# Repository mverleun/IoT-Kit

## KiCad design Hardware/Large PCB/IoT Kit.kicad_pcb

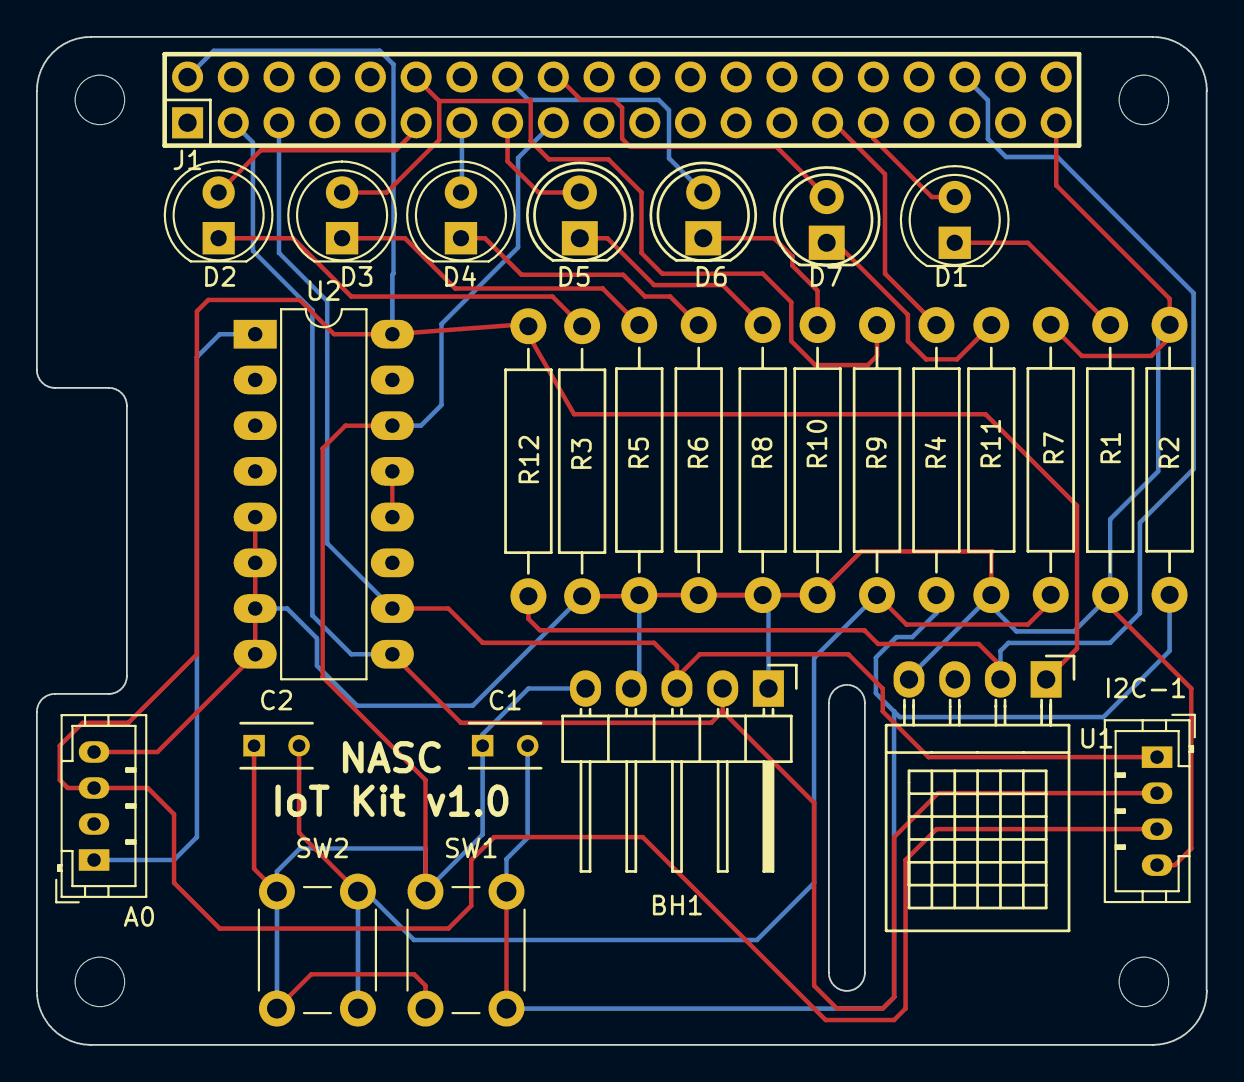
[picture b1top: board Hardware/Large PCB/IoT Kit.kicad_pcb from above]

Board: 2 copper layers, 65.0 x 56.0 mm, 29 parts (0 on the bottom side), 25 nets.

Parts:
A0: GROVE-CONNECTOR-DIP_4P-2.0_; JST_PH_B4B-PH-K_04x2.00mm_Straight
BH1: BH1750; Pin_Header_Angled_1x05
C1, C2: C; C_Rect_L4_W2.5_P2.5
D1: LED Geel; LED_D5.0mm
D2: LED Groen; LED_D5.0mm
D3, D4: LED Rood; LED_D5.0mm
D5, D6, D7: LED Rood; LED-5MM
I2C-1: GROVE-CONNECTOR-DIP_4P-2.0_; JST_PH_B4B-PH-K_04x2.00mm_Straight
J1: RPi_GPIO; Samtec_HLE-120-02-XXX-DV-BE-XX-XX
R1, R3, R5, R6, R8, R10, R11: 470; Resistor_Horizontal_RM15mm
R2, R7: 10K; Resistor_Horizontal_RM15mm
R4, R9: 1K; Resistor_Horizontal_RM15mm
R12: 4K7; Resistor_Horizontal_RM15mm
SW1, SW2: SW_Push; SW_PUSH_6mm_h9.5mm
U1: DHT11; Pin_Header_Angled_1x04
U2: PCF8591; DIP-16_W7.62mm_LongPads

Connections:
+3V3: BH1.5, C1.1, C2.1, J1.17, SW1.1, SW2.1, U2.14
+5V: A0.3, I2C-1.3, J1.2, R12.1, U1.1, U2.16
GNDA: U2.12, U2.13
GNDD: A0.4, BH1.1, BH1.4, I2C-1.4, J1.39, R1.2, R2.2, R3.2, R5.2, R6.2, R7.2, R8.2, R10.2, R11.2, U1.4, U2.5, U2.6, U2.7, U2.8
GPIO02-SDA1-I2C: BH1.2, I2C-1.2, J1.3, U2.9
GPIO03-SCL1-I2C: BH1.3, I2C-1.1, J1.5, U2.10
GPIO5: J1.29, R4.1
GPIO6: D1.2, J1.31
GPIO16: J1.36, R12.2, U1.2
GPIO17: D2.2, J1.11
GPIO18: D3.2, J1.12, R9.1
GPIO22: D5.2, J1.15
GPIO23: D6.2, J1.16
GPIO24: D7.2, J1.18
GPIO27: D4.2, J1.13
unnamed: A0.1, U2.1
unnamed: C1.2, R2.1, R4.2, SW1.2
unnamed: C2.2, R7.1, R9.2, SW2.2
unnamed: D1.1, R1.1
unnamed: D2.1, R3.1
unnamed: D3.1, R5.1
unnamed: D4.1, R6.1
unnamed: D5.1, R8.1
unnamed: D6.1, R10.1
unnamed: D7.1, R11.1

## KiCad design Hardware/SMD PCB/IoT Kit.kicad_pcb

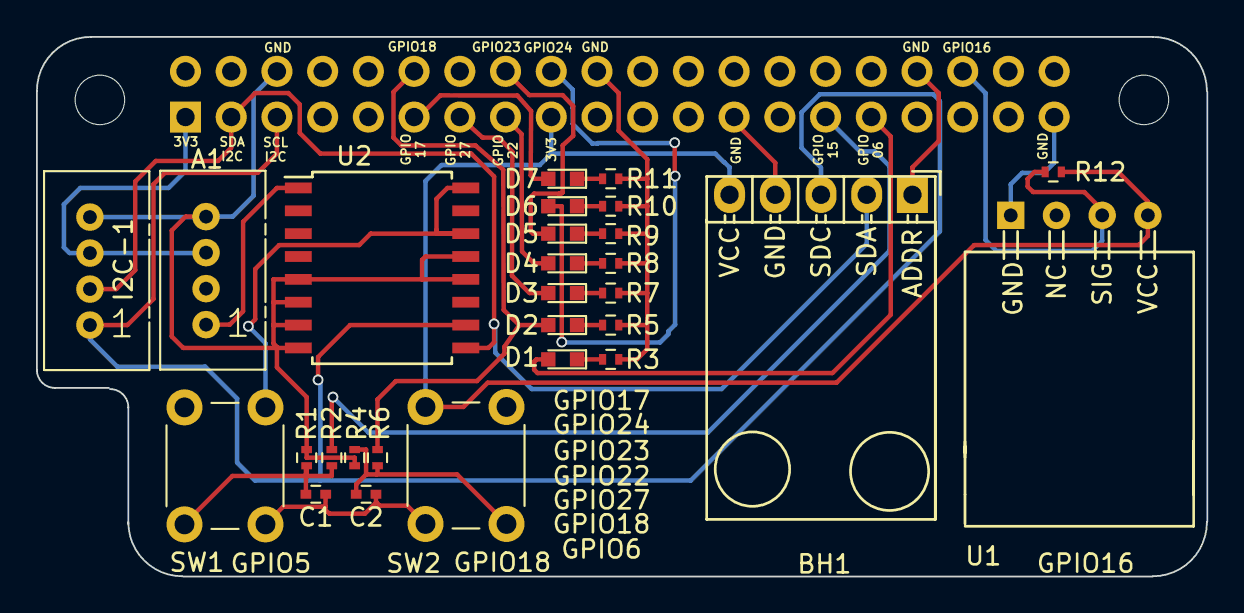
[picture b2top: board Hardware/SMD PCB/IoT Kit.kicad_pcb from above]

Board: 2 copper layers, 65.0 x 30.0 mm, 29 parts (0 on the bottom side), 24 nets.

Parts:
A1: JST-PH-2.0; Grove_1x04
BH1: BH1750 (GY-302); Pin_Header_Angled_1x05
C1, C2: 47nF; C_0402
D1: LED 6 Yellow; LED_0603
D2: LED 18 Red; LED_0603
D3: LED 27 Red; LED_0603
D4: LED 22 Red; LED_0603
D5: LED 23 Red; LED_0603
D6: LED 24 Red; LED_0603
D7: LED 17 Green; LED_0603
I2C-1: JST-PH-2.0; Grove_1x04
J1: RPi_GPIO; Pin_Header_Straight_2x20
R1, R4: 10K; R_0402
R2, R6: 1K; R_0402
R3, R5, R7, R8, R9, R10, R11: 470; R_0402
R12: 4K7; R_0402
SW1, SW2: SW_Push: JT 0102; SW_PUSH_6mm_h9.5mm
U1: DHT11
U2: PCF8591T; SOIC-16W_7.5x10.3mm_Pitch1.27mm

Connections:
+3V3: A1.3, BH1.5, C1.1, C2.1, I2C-1.3, J1.1, J1.17, R12.1, SW1.1, SW2.1, U1.4, U2.14, U2.16
+5V: J1.2, J1.4
GNDA: A1.4, BH1.1, BH1.4, I2C-1.4, J1.6, J1.9, J1.14, J1.20, J1.25, J1.30, J1.34, J1.39, R1.2, R3.2, R4.2, R5.2, R7.2, R8.2, R9.2, R10.2, R11.2, U1.1, U2.5, U2.6, U2.7, U2.8, U2.12, U2.13
GPIO02-SDA1-I2C: BH1.2, I2C-1.2, J1.3, U2.9
GPIO03-SCL1-I2C: BH1.3, I2C-1.1, J1.5, U2.10
GPIO5: J1.29, R2.1
GPIO6: D1.2, J1.31
GPIO16: J1.36, R12.2, U1.3
GPIO17: D7.2, J1.11
GPIO18: D2.2, J1.12, R6.1
GPIO22: D4.2, J1.15
GPIO23: D5.2, J1.16
GPIO24: D6.2, J1.18
GPIO27: D3.2, J1.13
unnamed: A1.1, U2.1
unnamed: C1.2, R1.1, R2.2, SW1.2
unnamed: C2.2, R4.1, R6.2, SW2.2
unnamed: D1.1, R3.1
unnamed: D2.1, R5.1
unnamed: D3.1, R7.1
unnamed: D4.1, R8.1
unnamed: D5.1, R9.1
unnamed: D6.1, R10.1
unnamed: D7.1, R11.1

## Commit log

2018-03-20 Started with DHT-11 sensor
2018-03-20 Created firmware for Wemos D1 with BH1750
2018-03-20 Renamed file
2018-04-02 1.0.1 02-04-2018 Updated libraries, added ui in /data, added code
2018-04-02 Removed ui to reduce spiffs size
2018-04-03 Verson 1.0 Initial commit
2018-04-03 1.0 Initial commit
2018-04-03 1.0 Initial release
2018-04-04 1.1 Added JSON output
2018-04-25 Add dusk boolean
2018-04-25 Changed license
2018-04-25 Added some url's
2018-04-25 Updated version number
2018-04-25 Added and I2C diagnostic firmware to do baseline testing with I2C shield. Added example config.json files
2018-04-28 Added documentation
2018-04-28 Started to document Software
2018-04-28 Improving documentation
2018-04-28 Updating Documentation
2018-04-28 Images
2018-04-28 Documentation
2018-04-28 Add images to documentation
2018-04-28 Documentation updated
2018-04-28 Cleaned up code
2018-04-28 Updated documentation
2018-04-28 Update documentation
2018-04-29 (Grav GitSync) Automatic Commit from mverleun
2018-04-29 Website test
2018-04-29 Website
2018-04-29 Replaced image
2018-05-08 Working motordriver
2018-05-10 Cleaned up code, added descriptive comments.
2018-05-10 Cleaned up code, added descriptive comments
2018-05-10 Renamed project folder
2018-05-10 Cleaned up more code
2018-05-25 Changed hardware setup into a table
2018-05-25 Fixed typo
2018-05-27 Corrected URL's
2018-05-31 Renamed OLED shield
2018-06-02 Modified platformio.ini
    Changes to move firmware to common builds directory
2018-06-03 Started on irrigation controller
2018-06-03 Renamed project
2018-06-03 Updated builds.
2018-06-03 Added branch system
2018-06-03 Removed P1 Meter
    Not ready yet
2018-06-03 Removed two firmwares
    Not yet ready. Still in development
2018-06-03 Cleaned up master
2018-06-03 Added code
2018-06-04 Added image
2018-06-04 Typo...
2018-06-04 Removed typo's
2018-06-06 Cleaned up JSON code
2018-06-06 Changed JSON config
2018-06-07 Test
2018-06-12 Added licenses
2018-06-12 Added schematics
2018-06-12 Ignore .elf files
2018-06-12 Remove .elf files
2018-06-20 Start with SSL
2018-06-27 Started to work on VCC reporting
2018-06-27 Changed GPIO to control sensor
2018-06-27 First attempt to implement SSL
2018-09-08 place homie and esphomelib in their own directories
2018-09-08 Added esphomelib config
2018-09-08 Added status led
2018-09-08 Add esphomelib config
2019-01-12 Cleaned up content
2019-01-12 Changed name
2019-04-12 Added PCB Schematics and design
2019-04-12 Removed two documents
2019-05-20 Reorganized directory
2019-05-20 Cleaned up a bit
2019-05-20 Added Python scripts
